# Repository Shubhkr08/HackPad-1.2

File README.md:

# HackPad-1.2
<br>
My personal micro pad for general shortcuts and game development, I am using 3 x 3 keys matrix and 9 diode (so it just needs 6 gpio pins) and 3 extra keys to switch between three different channels , so in total the micro pad can have a total of 3x9 = 27 output. It is based on XIAO RP2040<br><br>
**BOM**<br>
**#**
XIAO RP2040<br>
**#**
12 x MX-Style switches <br>
**#**
12 x Blank DSA keycaps<br>
**#**
9 x Through-hole 1N4148 Diodes <br>
**#**
4 x  M3x16mm screws <br>
**#**
4 x  M3x5mx4mm heatset inserts <br>

<br><br>
**Schematic**

<br><br>
**PCB**<br>

<br><br>
**Case**<br>

<br><br>
**Final Look**<br>

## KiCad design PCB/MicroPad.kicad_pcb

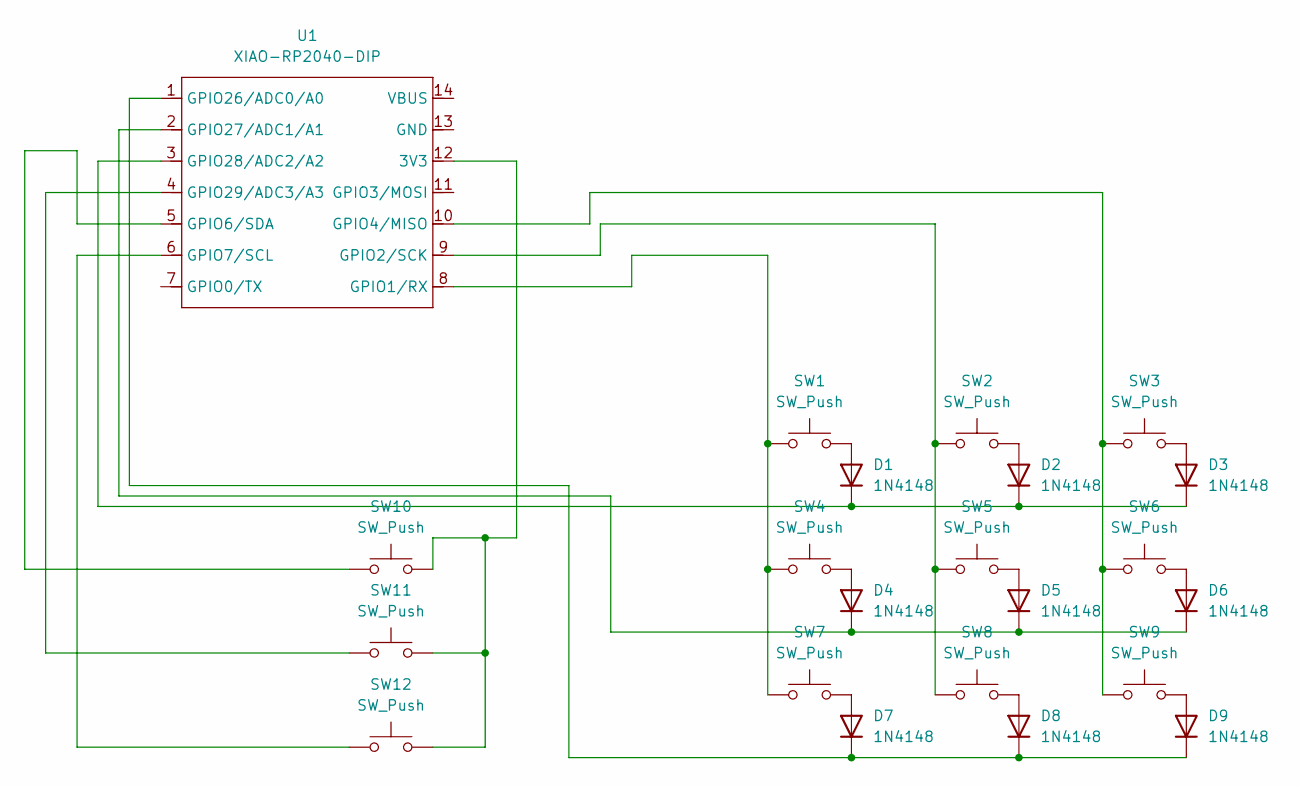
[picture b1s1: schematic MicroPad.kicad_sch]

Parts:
D1, D2, D3, D4, D5, D6, D7, D8, D9: 1N4148; D_DO-35_SOD27_P7.62mm_Horizontal
SW1, SW2, SW3, SW4, SW5, SW6, SW7, SW8, SW9, SW10, SW11, SW12: SW_Push; SW_Cherry_MX_1.00u_PCB
U1: XIAO-RP2040-DIP

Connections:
unnamed: D1.2 (A), SW1.2
unnamed: D1.1 (K), D2.1 (K), D3.1 (K), U1.3 (GPIO28/ADC2/A2)
unnamed: D2.2 (A), SW2.2
unnamed: D3.2 (A), SW3.2
unnamed: D4.2 (A), SW4.2
unnamed: D4.1 (K), D5.1 (K), D6.1 (K), U1.2 (GPIO27/ADC1/A1)
unnamed: D5.2 (A), SW5.2
unnamed: D6.2 (A), SW6.2
unnamed: D7.2 (A), SW7.2
unnamed: D7.1 (K), D8.1 (K), D9.1 (K), U1.1 (GPIO26/ADC0/A0)
unnamed: D8.2 (A), SW8.2
unnamed: D9.2 (A), SW9.2
unnamed: SW10.2, SW11.2, SW12.2, U1.12 (3V3)
unnamed: SW1.1, SW4.1, SW7.1, U1.8 (GPIO1/RX)
unnamed: SW2.1, SW5.1, SW8.1, U1.9 (GPIO2/SCK)
unnamed: SW3.1, SW6.1, SW9.1, U1.10 (GPIO4/MISO)
unnamed: SW10.1, U1.5 (GPIO6/SDA)
unnamed: SW12.1, U1.6 (GPIO7/SCL)
unnamed: SW11.1, U1.4 (GPIO29/ADC3/A3)

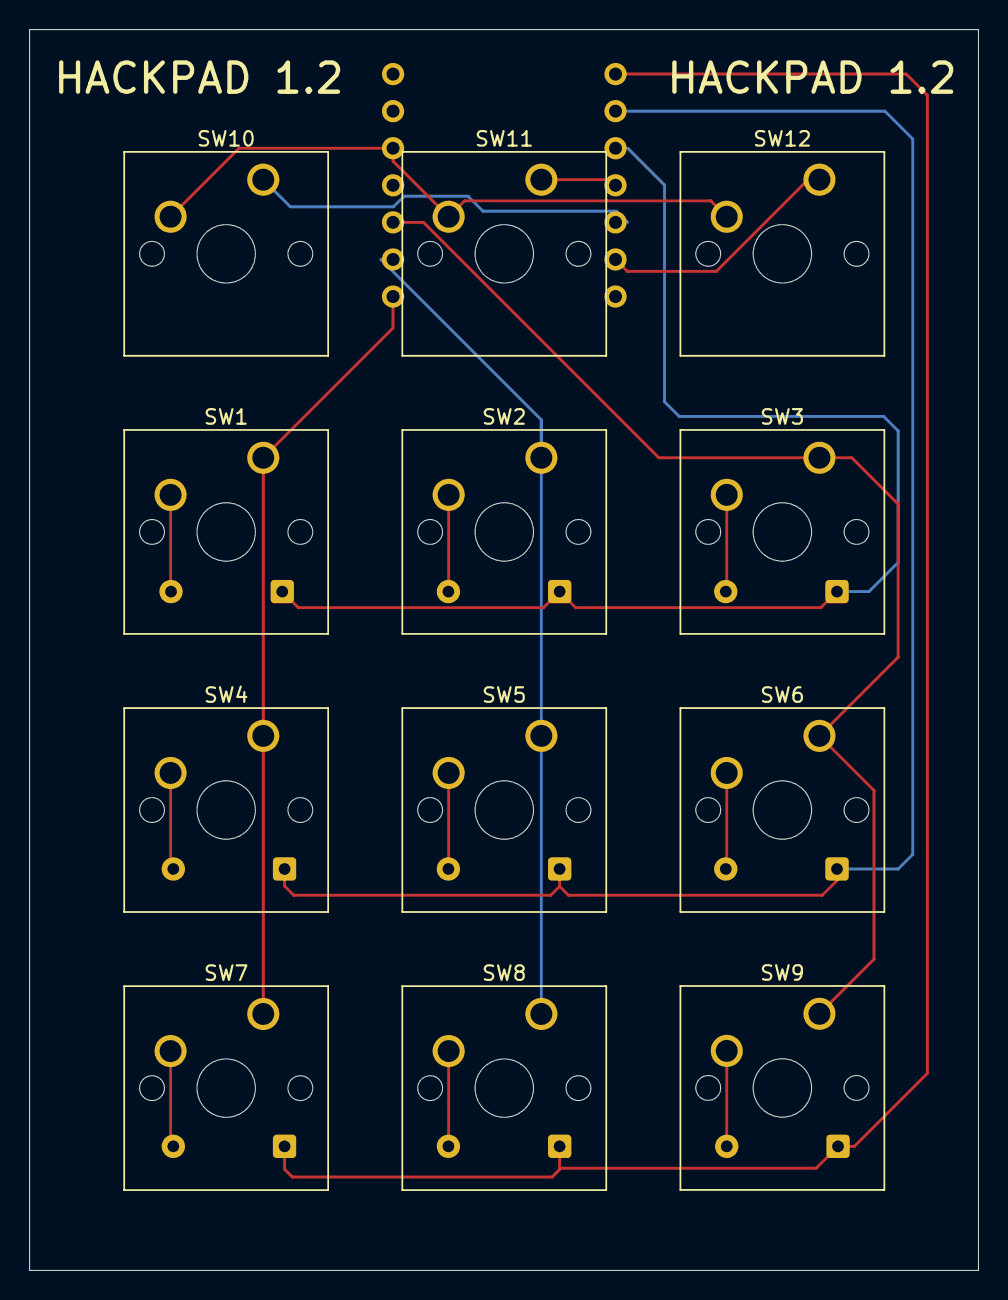
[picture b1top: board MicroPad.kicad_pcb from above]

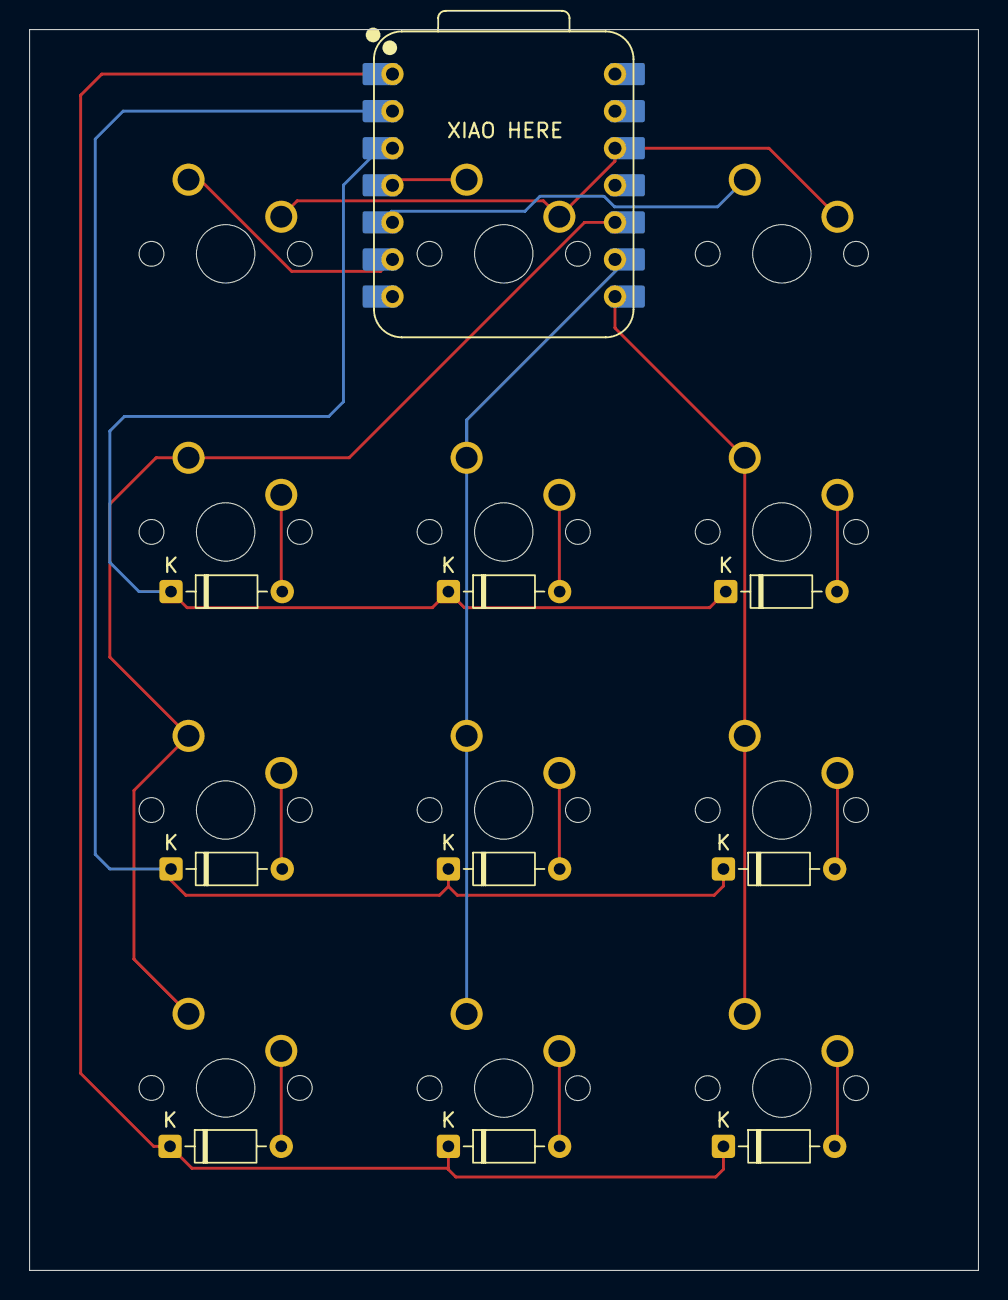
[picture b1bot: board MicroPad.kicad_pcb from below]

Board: 2 copper layers, 65.0 x 85.0 mm, 22 parts (10 on the bottom side), 19 nets.
